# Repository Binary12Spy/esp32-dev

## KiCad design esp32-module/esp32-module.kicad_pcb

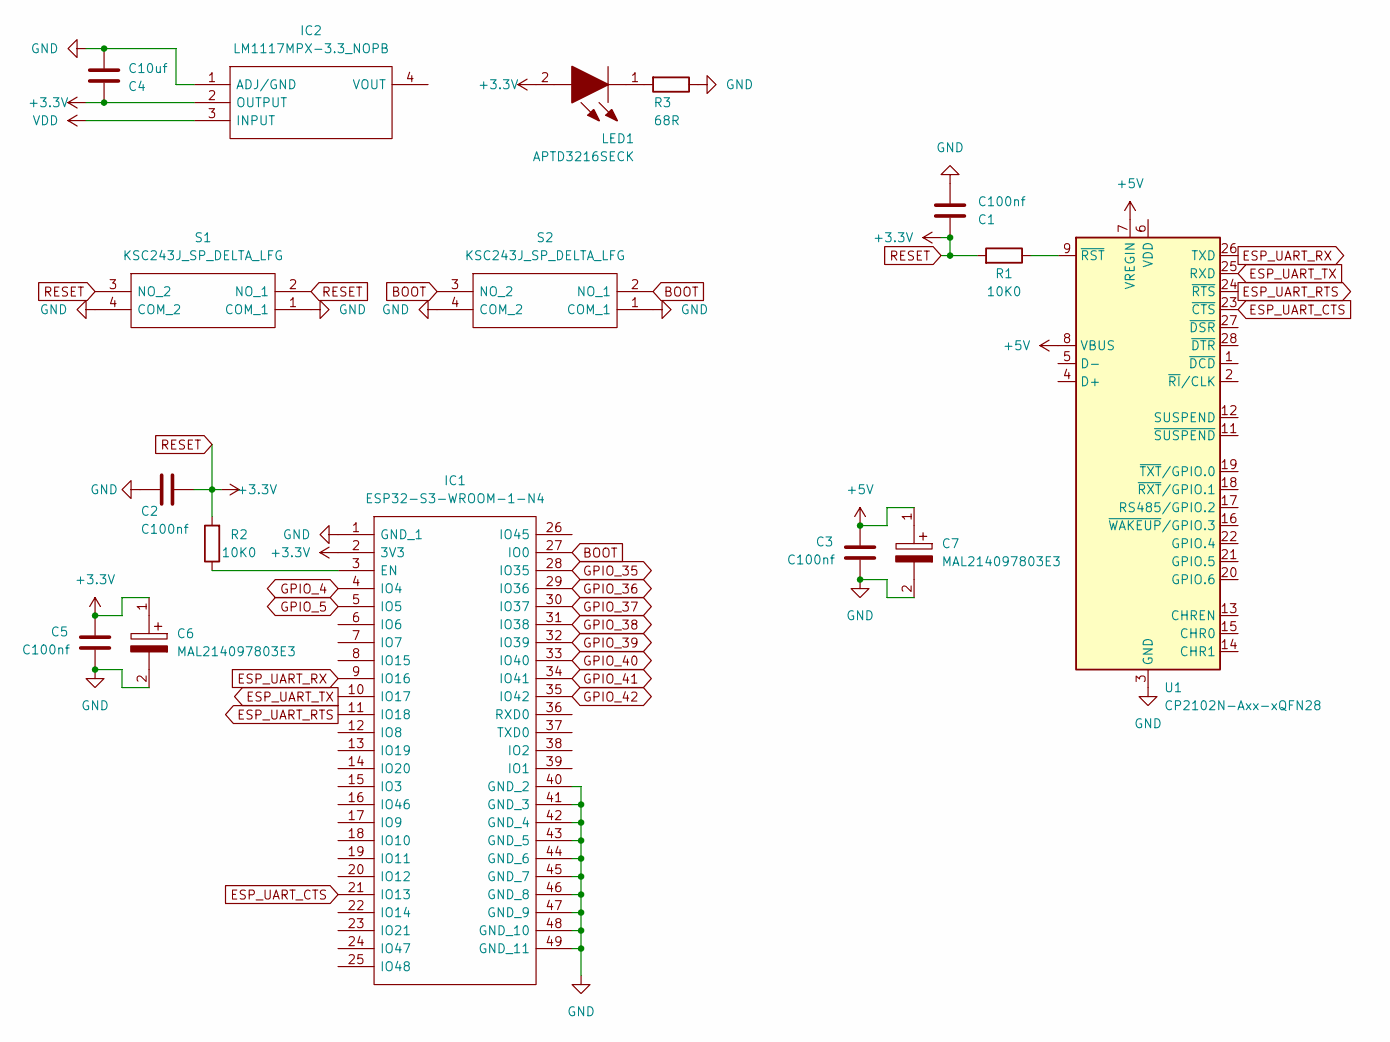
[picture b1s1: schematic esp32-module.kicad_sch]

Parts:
C1, C2, C3, C5: C100nf; C_0603_1608Metric
C4: C10uf; C_0603_1608Metric
C6, C7: MAL214097803E3; CAPAE850X1050N; Mouser Part Number 594-2222-140-97803
IC1: ESP32-S3-WROOM-1-N4; ESP32S3WROOM1UN8R8; Mouser Part Number 356-ESP32-S3WROOM1N4
IC2: LM1117MPX-3.3_NOPB; SOT230P700X180-4N; Mouser Part Number 926-LM1117MPX3.3NOPB
LED1: APTD3216SECK; Mouser Part Number 604-APTD-3216SECK
R1, R2: 10K0; R_1206_3216Metric
R3: 68R; R_1206_3216Metric
S1, S2: KSC243J_SP_DELTA_LFG; KSC243JSPDELTALFG; Manufacturer_Part_Number KSC243J SP DELTA LFG
U1: CP2102N-Axx-xQFN28; QFN-28-1EP_5x5mm_P0.5mm_EP3.35x3.35mm

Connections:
+5V: C3.1, C7.1, U1.7 (VREGIN), U1.8 (VBUS)
BOOT: IC1.27 (IO0), S2.2 (NO_1), S2.3 (NO_2)
ESP_UART_CTS: IC1.21 (IO13), U1.23 (~CTS)
ESP_UART_RTS: IC1.11 (IO18), U1.24 (~RTS)
ESP_UART_RX: IC1.9 (IO16), U1.26 (TXD)
ESP_UART_TX: IC1.10 (IO17), U1.25 (RXD)
GND: C1.2, C2.2, C3.2, C4.1, C5.2, C6.2, C7.2, IC1.1 (GND_1), IC1.40 (GND_2), IC1.41 (GND_3), IC1.42 (GND_4), IC1.43 (GND_5), IC1.44 (GND_6), IC1.45 (GND_7), IC1.46 (GND_8), IC1.47 (GND_9), IC1.48 (GND_10), IC1.49 (GND_11), IC2.1 (ADJ/GND), R3.1, S1.1 (COM_1), S1.4 (COM_2), S2.1 (COM_1), S2.4 (COM_2), U1.3 (GND), U1.29 (GND)
GPIO_4: IC1.4 (IO4)
GPIO_5: IC1.5 (IO5)
GPIO_35: IC1.28 (IO35)
GPIO_36: IC1.29 (IO36)
GPIO_37: IC1.30 (IO37)
GPIO_38: IC1.31 (IO38)
GPIO_39: IC1.32 (IO39)
GPIO_40: IC1.33 (IO40)
GPIO_41: IC1.34 (IO41)
GPIO_42: IC1.35 (IO42)
unnamed: IC1.3 (EN), R2.1
unnamed: LED1.1, R3.2
unnamed: R1.1, U1.9 (~RST)
RESET: C1.1, C2.1, C4.2, C5.1, C6.1, IC1.2 (3V3), IC2.2 (OUTPUT), LED1.2, R1.2, R2.2, S1.2 (NO_1), S1.3 (NO_2)
VDD: IC2.3 (INPUT)

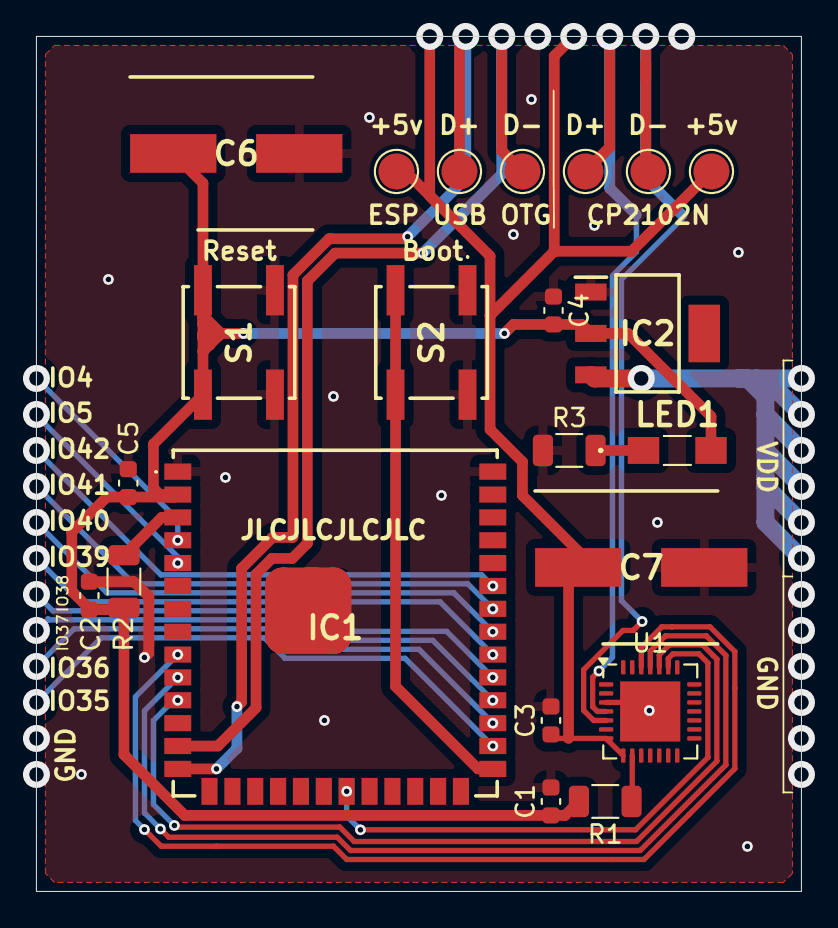
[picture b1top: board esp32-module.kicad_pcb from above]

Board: 2 copper layers, 42.5 x 47.5 mm, 16 parts (0 on the bottom side), 11 nets.

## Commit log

2024-10-01 Initial esp32-module implementation
2024-10-02 Further Implementation
